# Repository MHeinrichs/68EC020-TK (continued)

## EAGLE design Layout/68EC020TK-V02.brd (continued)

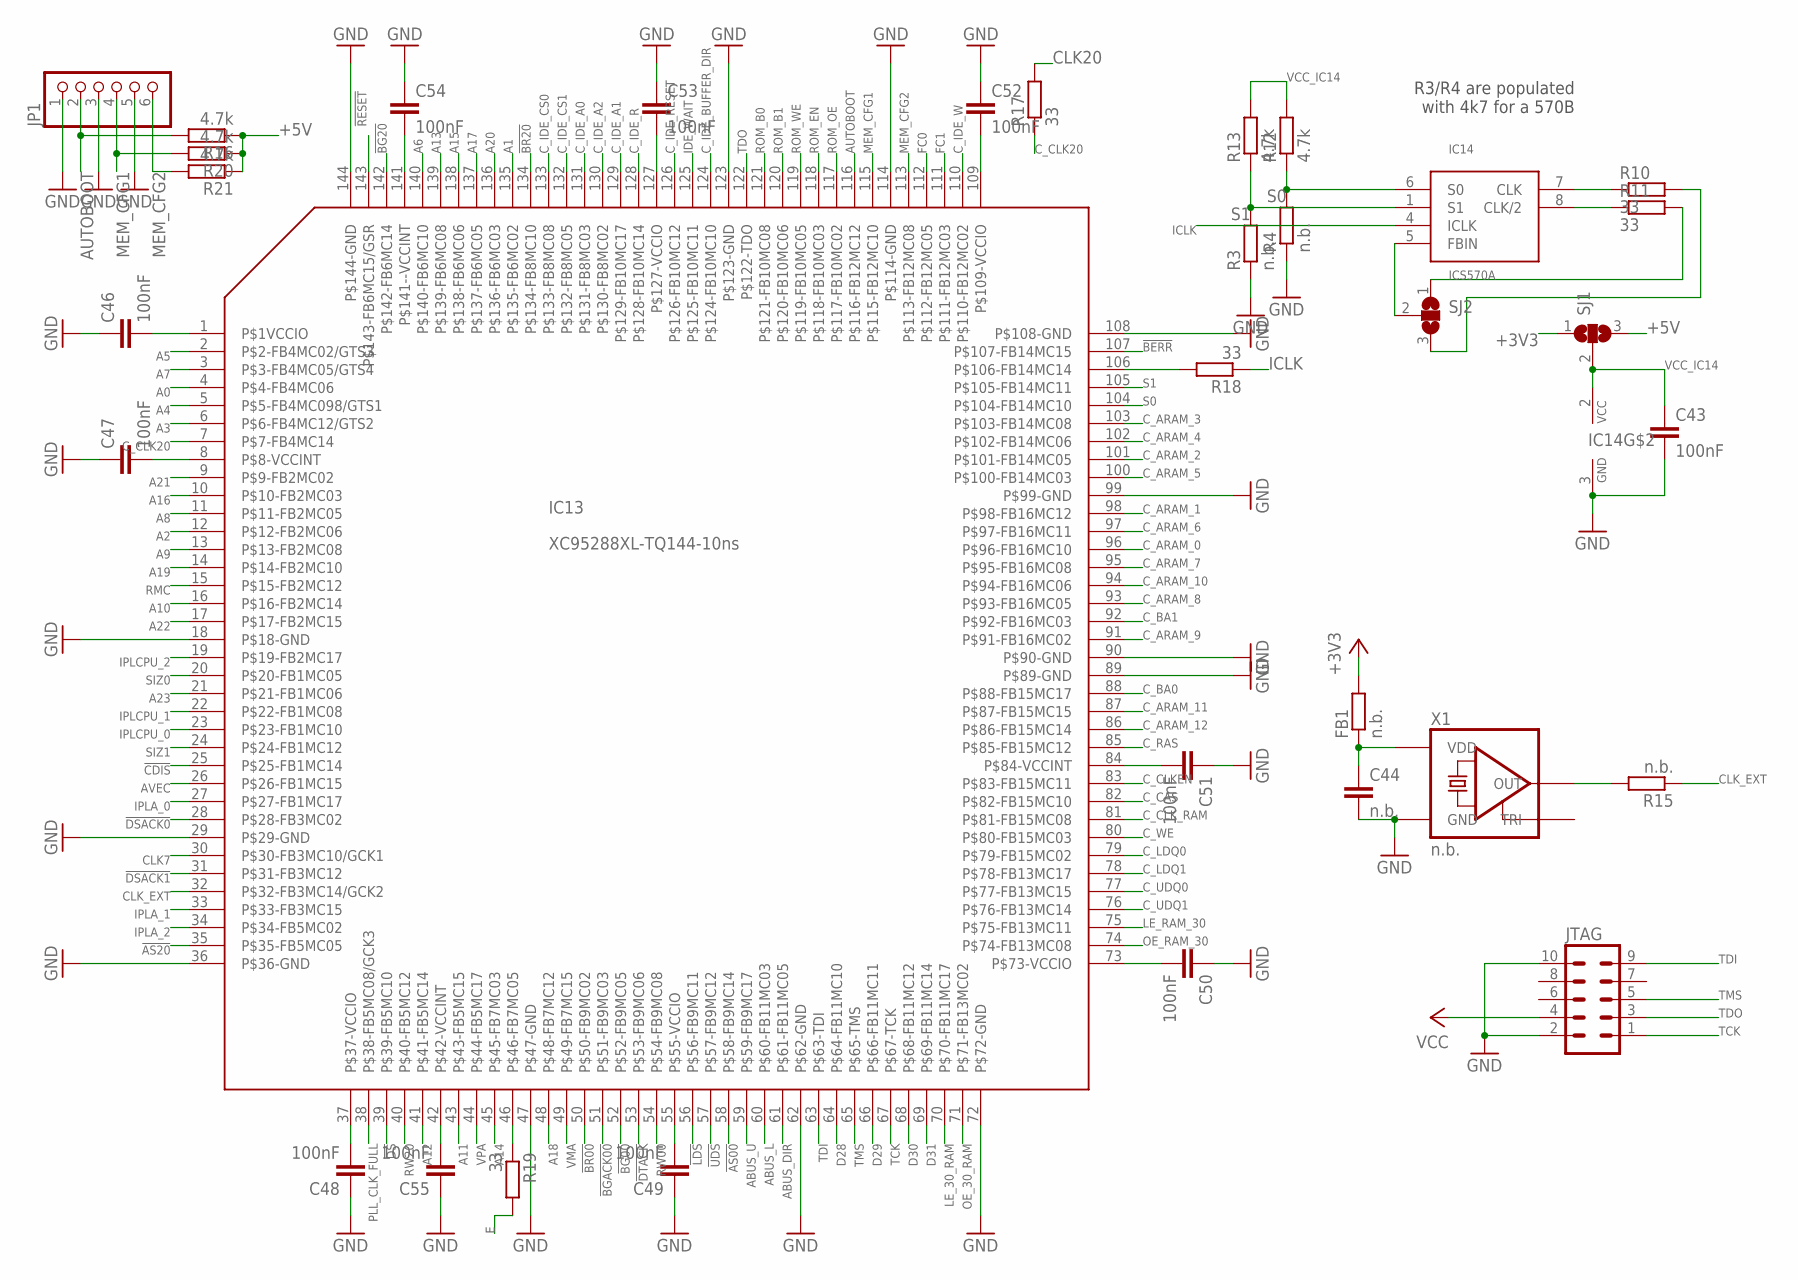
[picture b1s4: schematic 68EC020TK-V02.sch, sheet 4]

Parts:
C43, C46, C47, C48, C49, C50, C51, C52, C53, C54, C55: 100nF; C0603K
C44: n.b.; C0603K
FB1: n.b.; R0603
IC13: XC95288XL-TQ144-10ns; TQFP144
IC14: ICS570A; SO-8
JP1: PINHD-1X6/90; 1X06/90
JTAG: ML10
R3, R4, R15: n.b.; R0603
R10, R11, R17, R18, R19: 33; R0603
R12, R13, R16, R20, R21: 4.7k; R0603
SJ1, SJ2: SJ2W; SJ_2
X1: n.b.; 7X5

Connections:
!AS00: IC13.58 (P$58-FB9MC14); also elsewhere on the board
!AS20: IC13.35 (P$35-FB5MC05); also elsewhere on the board
!BERR: IC13.107 (P$107-FB14MC15); also elsewhere on the board
!BG00: IC13.52 (P$52-FB9MC05); also elsewhere on the board
!BG20: IC13.142 (P$142-FB6MC14); also elsewhere on the board
!BGACK00: IC13.51 (P$51-FB9MC03); also elsewhere on the board
!BR00: IC13.50 (P$50-FB9MC02); also elsewhere on the board
!BR20: IC13.134 (P$134-FB8MC10); also elsewhere on the board
!CDIS: IC13.25 (P$25-FB1MC14); also elsewhere on the board
!DS: IC13.39 (P$39-FB5MC10); also elsewhere on the board
!DSACK0: IC13.28 (P$28-FB3MC02); also elsewhere on the board
!DSACK1: IC13.31 (P$31-FB3MC12); also elsewhere on the board
!DTACK: IC13.53 (P$53-FB9MC06); also elsewhere on the board
!LDS: IC13.56 (P$56-FB9MC11); also elsewhere on the board
!RESET: IC13.143 (P$143-FB6MC15/GSR); also elsewhere on the board
!UDS: IC13.57 (P$57-FB9MC12); also elsewhere on the board
+3V3: C46.2, C47.2, C48.2, C49.2, C50.2, C51.2, C52.2, C53.2, C54.2, C55.2, FB1.2, IC13.1 (P$1VCCIO), IC13.8 (P$8-VCCINT), IC13.37 (P$37-VCCIO), IC13.42 (P$42-VCCINT), IC13.55 (P$55-VCCIO), IC13.73 (P$73-VCCIO), IC13.84 (P$84-VCCINT), IC13.109 (P$109-VCCIO), IC13.127 (P$127-VCCIO), IC13.141 (P$141--VCCINT), SJ1.1; also elsewhere on the board
+5V: JTAG.4, R16.1, R20.1, R21.1, SJ1.3; also elsewhere on the board
A0: IC13.4 (P$4-FB4MC06); also elsewhere on the board
A1: IC13.135 (P$135-FB6MC02); also elsewhere on the board
A2: IC13.12 (P$12-FB2MC06); also elsewhere on the board
A3: IC13.6 (P$6-FB4MC12/GTS2); also elsewhere on the board
A4: IC13.5 (P$5-FB4MC098/GTS1); also elsewhere on the board
A5: IC13.2 (P$2-FB4MC02/GTS3); also elsewhere on the board
A6: IC13.140 (P$140-FB6MC10); also elsewhere on the board
A7: IC13.3 (P$3-FB4MC05/GTS4); also elsewhere on the board
A8: IC13.11 (P$11-FB2MC05); also elsewhere on the board
A9: IC13.13 (P$13-FB2MC08); also elsewhere on the board
A10: IC13.16 (P$16-FB2MC14); also elsewhere on the board
A11: IC13.43 (P$43-FB5MC15); also elsewhere on the board
A12: IC13.41 (P$41-FB5MC14); also elsewhere on the board
A13: IC13.139 (P$139-FB6MC08); also elsewhere on the board
A14: IC13.45 (P$45-FB7MC03); also elsewhere on the board
A15: IC13.138 (P$138-FB6MC06); also elsewhere on the board
A16: IC13.10 (P$10-FB2MC03); also elsewhere on the board
A17: IC13.137 (P$137-FB6MC05); also elsewhere on the board
A18: IC13.48 (P$48-FB7MC12); also elsewhere on the board
A19: IC13.14 (P$14-FB2MC10); also elsewhere on the board
A20: IC13.136 (P$136-FB6MC03); also elsewhere on the board
A21: IC13.9 (P$9-FB2MC02); also elsewhere on the board
A22: IC13.17 (P$17-FB2MC15); also elsewhere on the board
A23: IC13.21 (P$21-FB1MC06); also elsewhere on the board
ABUS_DIR: IC13.61 (P$61-FB11MC05); also elsewhere on the board
ABUS_L: IC13.60 (P$60-FB11MC03); also elsewhere on the board
ABUS_U: IC13.59 (P$59-FB9MC17); also elsewhere on the board
AUTOBOOT: IC13.116 (P$116-FB12MC12), JP1.2, R16.2
AVEC: IC13.26 (P$26-FB1MC15); also elsewhere on the board
CLK7: IC13.30 (P$30-FB3MC10/GCK1); also elsewhere on the board
CLK20: R17.2; also elsewhere on the board
CLK_EXT: IC13.32 (P$32-FB3MC14/GCK2), R15.1
C_ARAM_0: IC13.96 (P$96-FB16MC10); also elsewhere on the board
C_ARAM_1: IC13.98 (P$98-FB16MC12); also elsewhere on the board
C_ARAM_2: IC13.101 (P$101-FB14MC05); also elsewhere on the board
C_ARAM_3: IC13.103 (P$103-FB14MC08); also elsewhere on the board
C_ARAM_4: IC13.102 (P$102-FB14MC06); also elsewhere on the board
C_ARAM_5: IC13.100 (P$100-FB14MC03); also elsewhere on the board
C_ARAM_6: IC13.97 (P$97-FB16MC11); also elsewhere on the board
C_ARAM_7: IC13.95 (P$95-FB16MC08); also elsewhere on the board
C_ARAM_8: IC13.93 (P$93-FB16MC05); also elsewhere on the board
C_ARAM_9: IC13.91 (P$91-FB16MC02); also elsewhere on the board
C_ARAM_10: IC13.94 (P$94-FB16MC06); also elsewhere on the board
C_ARAM_11: IC13.87 (P$87-FB15MC15); also elsewhere on the board
C_ARAM_12: IC13.86 (P$86-FB15MC14); also elsewhere on the board
C_BA0: IC13.88 (P$88-FB15MC17); also elsewhere on the board
C_BA1: IC13.92 (P$92-FB16MC03); also elsewhere on the board
C_CAS: IC13.82 (P$82-FB15MC10); also elsewhere on the board
C_CLK20: IC13.7 (P$7-FB4MC14), R17.1
C_CLKEN: IC13.83 (P$83-FB15MC11); also elsewhere on the board
C_CLK_RAM: IC13.81 (P$81-FB15MC08); also elsewhere on the board
C_IDE_A0: IC13.131 (P$131-FB8MC03); also elsewhere on the board
C_IDE_A1: IC13.129 (P$129-FB10MC17); also elsewhere on the board
C_IDE_A2: IC13.130 (P$130-FB8MC02); also elsewhere on the board
C_IDE_BUFFER_DIR: IC13.124 (P$124-FB10MC10); also elsewhere on the board
C_IDE_CS0: IC13.133 (P$133-FB8MC08); also elsewhere on the board
C_IDE_CS1: IC13.132 (P$132-FB8MC05); also elsewhere on the board
C_IDE_R: IC13.128 (P$128-FB10MC14); also elsewhere on the board
C_IDE_RESET: IC13.126 (P$126-FB10MC12); also elsewhere on the board
C_IDE_W: IC13.110 (P$110-FB12MC02); also elsewhere on the board
C_LDQ0: IC13.79 (P$79-FB15MC02); also elsewhere on the board
C_LDQ1: IC13.78 (P$78-FB13MC17); also elsewhere on the board
C_RAS: IC13.85 (P$85-FB15MC12); also elsewhere on the board
C_UDQ0: IC13.77 (P$77-FB13MC15); also elsewhere on the board
C_UDQ1: IC13.76 (P$76-FB13MC14); also elsewhere on the board
C_WE: IC13.80 (P$80-FB15MC03); also elsewhere on the board
D28: IC13.64 (P$64-FB11MC10); also elsewhere on the board
D29: IC13.66 (P$66-FB11MC11); also elsewhere on the board
D30: IC13.68 (P$68-FB11MC12); also elsewhere on the board
D31: IC13.69 (P$69-FB11MC14); also elsewhere on the board
E: R19.2; also elsewhere on the board
FC0: IC13.112 (P$112-FB12MC05); also elsewhere on the board
FC1: IC13.111 (P$111-FB12MC03); also elsewhere on the board
GND: C43.2, C44.2, C46.1, C47.1, C48.1, C49.1, C50.1, C51.1, C52.1, C53.1, C54.1, C55.1, IC13.18 (P$18-GND), IC13.29 (P$29-GND), IC13.36 (P$36-GND), IC13.47 (P$47-GND), IC13.62 (P$62-GND), IC13.72 (P$72-GND), IC13.89 (P$89-GND), IC13.90 (P$90-GND), IC13.99 (P$99-GND), IC13.108 (P$108-GND), IC13.114 (P$114-GND), IC13.123 (P$123-GND), IC13.144 (P$144-GND), IC14.3 (GND), JP1.1, JP1.3, JP1.5, JTAG.2, JTAG.10, R3.1, R4.1, X1.P$2 (GND); also elsewhere on the board
ICLK: IC14.4 (ICLK), R18.1
IDE_WAIT: IC13.125 (P$125-FB10MC11); also elsewhere on the board
IPLA_0: IC13.27 (P$27-FB1MC17); also elsewhere on the board
IPLA_1: IC13.33 (P$33-FB3MC15); also elsewhere on the board
IPLA_2: IC13.34 (P$34-FB5MC02); also elsewhere on the board
IPLCPU_0: IC13.23 (P$23-FB1MC10); also elsewhere on the board
IPLCPU_1: IC13.22 (P$22-FB1MC08); also elsewhere on the board
IPLCPU_2: IC13.19 (P$19-FB2MC17); also elsewhere on the board
LE_30_RAM: IC13.70 (P$70-FB11MC17); also elsewhere on the board
LE_RAM_30: IC13.75 (P$75-FB13MC11); also elsewhere on the board
MEM_CFG1: IC13.115 (P$115-FB12MC10), JP1.4, R20.2
MEM_CFG2: IC13.113 (P$113-FB12MC08), JP1.6, R21.2
unnamed: IC13.106 (P$106-FB14MC14), R18.2
unnamed: IC14.7 (CLK), R10.1
unnamed: IC14.8 (CLK/2), R11.1
unnamed: IC13.46 (P$46-FB7MC05), R19.1
unnamed: IC14.5 (FBIN), SJ2.2
unnamed: R15.2, X1.P$3 (OUT)
OE_30_RAM: IC13.71 (P$71-FB13MC02); also elsewhere on the board
OE_RAM_30: IC13.74 (P$74-FB13MC08); also elsewhere on the board
PLL_CLK_FULL: IC13.38 (P$38-FB5MC08/GCK3), R10.2, SJ2.3
PLL_CLK_HALF: R11.2, SJ2.1
RMC: IC13.15 (P$15-FB2MC12); also elsewhere on the board
ROM_B0: IC13.121 (P$121-FB10MC08); also elsewhere on the board
ROM_B1: IC13.120 (P$120-FB10MC06); also elsewhere on the board
ROM_EN: IC13.118 (P$118-FB10MC03); also elsewhere on the board
ROM_OE: IC13.117 (P$117-FB10MC02); also elsewhere on the board
ROM_WE: IC13.119 (P$119-FB10MC05); also elsewhere on the board
RW00: IC13.54 (P$54-FB9MC08); also elsewhere on the board
RW20: IC13.40 (P$40-FB5MC12); also elsewhere on the board
S0: IC13.104 (P$104-FB14MC10), IC14.6 (S0), R4.2, R12.1
S1: IC13.105 (P$105-FB14MC11), IC14.1 (S1), R3.2, R13.1
SIZ0: IC13.20 (P$20-FB1MC05); also elsewhere on the board
SIZ1: IC13.24 (P$24-FB1MC12); also elsewhere on the board
TCK: IC13.67 (P$67-TCK), JTAG.1
TDI: IC13.63 (P$63-TDI), JTAG.9
TDO: IC13.122 (P$122-TDO), JTAG.3
TMS: IC13.65 (P$65-TMS), JTAG.5
VCC-X: C44.1, FB1.1, X1.P$4 (VDD)
VCC_IC14: C43.1, IC14.2 (VCC), R12.2, R13.2, SJ1.2
VMA: IC13.49 (P$49-FB7MC15); also elsewhere on the board
VPA: IC13.44 (P$44-FB5MC17); also elsewhere on the board

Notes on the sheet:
R3/R4 are populated with 4k7 for a 570B

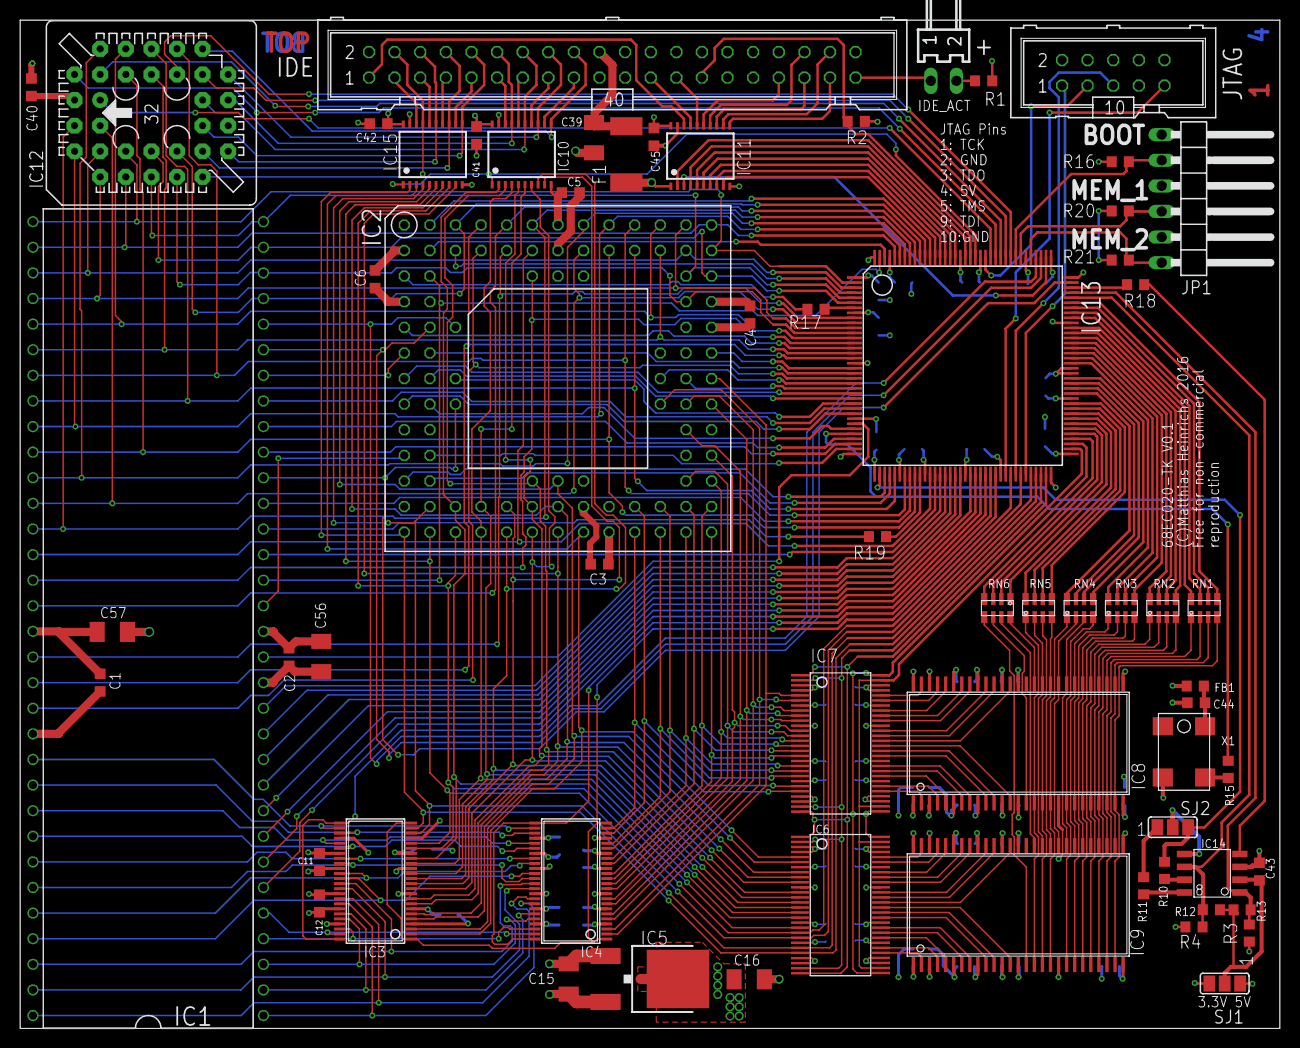
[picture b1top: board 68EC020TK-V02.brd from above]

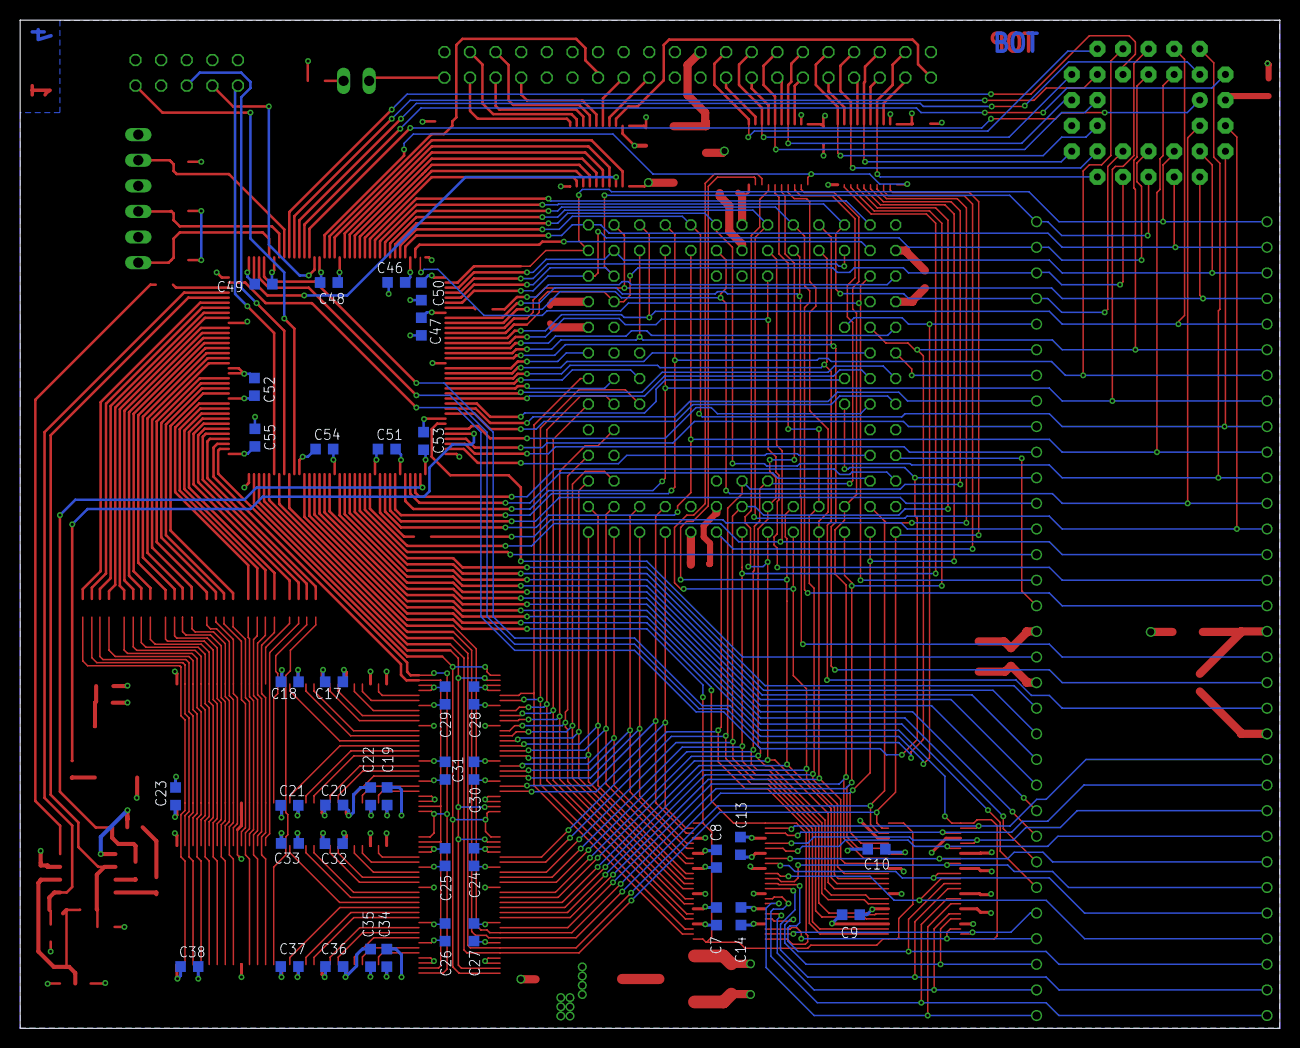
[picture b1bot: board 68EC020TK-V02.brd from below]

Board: 4 copper layers, 124.9 x 100.0 mm, 102 parts (38 on the bottom side), 263 nets.

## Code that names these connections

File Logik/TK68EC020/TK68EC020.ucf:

NET "A_0" 					LOC = "P4"; 
NET "A<1>"	 				LOC = "P135"; 
NET "A<2>"	 				LOC = "P12"; 
NET "A<3>"	 				LOC = "P6"; 
NET "A<4>"	 				LOC = "P5"; 
NET "A<5>"	 				LOC = "P2"; 
NET "A<6>"	 				LOC = "P140"; 
NET "A<7>"	 				LOC = "P3"; 
NET "A<8>"	 				LOC = "P11"; 
NET "A<9>"	 				LOC = "P13"; 
NET "A<10>"					LOC = "P16"; 
NET "A<11>"					LOC = "P43"; 
NET "A<12>"	 				LOC = "P41"; 
NET "A<13>"	 				LOC = "P139"; 
NET "A<14>"	 				LOC = "P45"; 
NET "A<15>"	 				LOC = "P138"; 
NET "A<16>"	 				LOC = "P10"; 
NET "A<17>"	 				LOC = "P137"; 
NET "A<18>"	 				LOC = "P48"; 
NET "A<19>"	 				LOC = "P14"; 
NET "A<20>"	 				LOC = "P136"; 
NET "A<21>"	 				LOC = "P9"; 
NET "A<22>"	 				LOC = "P17"; 
NET "A<23>"	 				LOC = "P21"; 
NET "ARAM<0>"				LOC = "P96"; 
NET "ARAM<1>"				LOC = "P98"; 
NET "ARAM<2>"				LOC = "P101"; 
NET "ARAM<3>"				LOC = "P103"; 
NET "ARAM<4>"				LOC = "P102"; 
NET "ARAM<5>"				LOC = "P100"; 
NET "ARAM<6>"				LOC = "P97"; 
NET "ARAM<7>"				LOC = "P95"; 
NET "ARAM<8>"				LOC = "P93"; 
NET "ARAM<9>"				LOC = "P91"; 
NET "ARAM<10>"			LOC = "P94"; 
NET "ARAM<11>"			LOC = "P87"; 
NET "ARAM<12>"			LOC = "P86"; 
NET "BA<0>"					LOC = "P88"; 
NET "BA<1>"					LOC = "P92"; 
NET "CAS" 					LOC = "P82"; 
NET "CLK_EN"				LOC = "P83"; 
NET "CLK_RAM"				LOC = "P81"; 
NET "LDQ0" 					LOC = "P79"; 
NET "LDQ1" 					LOC = "P78"; 
NET "UDQ0" 					LOC = "P77"; 
NET "UDQ1" 					LOC = "P76";
NET "LE_020_RAM"		LOC = "P70"; 
NET "LE_RAM_020"		LOC = "P75"; 
NET "MEM_WE" 				LOC = "P80"; 
NET "OE_020_RAM"		LOC = "P71"; 
NET "OE_RAM_020"		LOC = "P74"; 
NET "RAS"						LOC = "P85"; 
NET "D<28>"					LOC = "P64"; 
NET "D<29>"					LOC = "P66"; 
NET "D<30>"					LOC = "P68"; 
NET "D<31>"					LOC = "P69"; 
NET "IDE_A<0>"			LOC = "P131"; 
NET "IDE_A<1>"			LOC = "P129"; 
NET "IDE_A<2>"			LOC = "P130"; 
NET "IDE_CS<0>"			LOC = "P133"; 
NET "IDE_CS<1>"			LOC = "P132"; 
NET "IDE_BUF_DIR"					LOC = "P124"; 
NET "IDE_RESET"			LOC = "P126"; 
NET "IDE_R"					LOC = "P128"; 
NET "IDE_W"					LOC = "P110"; 
NET "IDE_WAIT" 			LOC = "P125"; 
NET "ROM_B<0>"			LOC = "P121"; 
NET "ROM_B<1>"			LOC = "P120"; 
NET "ROM_EN" 				LOC = "P118"; 
NET "ROM_OE" 				LOC = "P117"; 
NET "ROM_WE" 				LOC = "P119"; 
NET "RW_020" 				LOC = "P40"; 
NET "S<0>"					LOC = "P104"; 
NET "S<1>"					LOC = "P105"; 
NET "SIZE<0>"				LOC = "P20"; 
NET "SIZE<1>"				LOC = "P24"; 
NET "AS_020" 				LOC = "P35"; 
NET "DS_020" 				LOC = "P39"; 
NET "DSACK<0>"			LOC = "P28"; 
NET "DSACK<1>"			LOC = "P31"; 
NET "AS_000" 				LOC = "P58"; 
NET "RW_000" 				LOC = "P54"; 
NET "UDS_000" 			LOC = "P57"; 
NET "LDS_000" 			LOC = "P56"; 
NET "BG_020"				LOC = "P142"; 
NET "BG_000"				LOC = "P52"; 
NET "BGACK_000"			LOC = "P51"; 
NET "BR_020"				LOC = "P134"; 
NET "BR_000"				LOC = "P50"; 
NET "CLK_020" 			LOC = "P7"; 
NET "CLK_000" 			LOC = "P30"; 
NET "CLK_OSZI"			LOC = "P32"; 
NET "CLK_PLL_REF"		LOC = "P106"; 
NET "CLK_PLL" 			LOC = "P38"; 
NET "IPL_020<0>"		LOC = "P23"; 
NET "IPL_020<1>"		LOC = "P22"; 
NET "IPL_020<2>"		LOC = "P19"; 
NET "IPL_000<0>"		LOC = "P27"; 
NET "IPL_000<1>"		LOC = "P33"; 
NET "IPL_000<2>"		LOC = "P34"; 
NET "CDIS"					LOC = "P25"; 
NET "DTACK" 				LOC = "P53"; 
NET "AVEC" 					LOC = "P26"; 
NET "E" 						LOC = "P46"; 
NET "VMA" 					LOC = "P49"; 
NET "VPA" 					LOC = "P44"; 
NET "RW_020"				LOC = "P40"; 
NET "RESET"					LOC = "P143"; 
NET "MEM_CFG<0>"			LOC = "P115"; 
NET "MEM_CFG<1>"			LOC = "P113"; 
NET "AUTO_BOOT"			LOC = "P116"; 
NET "FC<0>"			LOC = "P112"; 
NET "FC<1>"			LOC = "P111"; 
NET "BERR"			LOC = "P107"; 
NET "AMIGA_BUS_DATA_DIR"		LOC = "P61"; 
NET "AMIGA_BUS_ENABLE_LOW"	LOC = "P60"; 
NET "AMIGA_BUS_ENABLE_HIGH"	LOC = "P59";
#Created by Constraints Editor (xc95288xl-tq144-10) - 2018/01/01
NET "CLK_PLL" TNM_NET = CLK_PLL;
TIMESPEC TS_CLK_PLL = PERIOD "CLK_PLL" 112 MHz HIGH 50%;

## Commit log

2017-09-20 :confetti_ball: Added .gitattributes & .gitignore files
2017-09-20 Initial push
2017-09-20 bus & autoconfig OK IDE-RW-fix but IDE& mem not working
2017-09-21 IDe & Atoboot working
2017-09-21 improved
2017-09-24 Working!
2017-09-24 rangermem enabled
2017-09-24 9.5MB working
2017-09-24 fixed ram config jumpers
2017-09-25 Adjusted resistor nets
2017-09-25 QFP100-design
2017-09-26 Fixed some Packages
2017-09-26 Working at 28MHz Sync to Amiga
2017-09-29 fixed parts but mem cfg not bug free
2017-09-29 Mem-cfg bug found: AC_Cycle_end was not updated
2017-09-29 Version under Test
2017-10-16 Sync improved but DMA not jet working
2017-12-18 570b-fix and e-clock rework
2018-01-01 DMA BR/BGACK improved E-Clock synced to pos edge but DMA-Cycle does not finish!
2018-01-03 DMA Working!
2018-01-03 Clean up
2018-01-03 Grr NOT working without DMA GRRRRR
2018-01-04 Working IDE was corrupt ;)
2018-01-04 Timing quirk for IDE: 1Ws for better stability
2018-01-04 Pics added
2018-01-10 DMA for fallback improved but in turbo mode a bug exisits :(
2018-01-10 Working in all possible configs :dancer:
2018-01-18 Improved layout
2018-01-18 fixed DMA-bug and removed memregion $B0-$B8
2019-08-28 Moved to gitlab
